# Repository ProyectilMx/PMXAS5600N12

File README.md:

PMXAS5600N12
Encoder Absoluto basado en el integrado AS5600 con 12 neopixels, configurable a través 
de COM Serial 9600 baudios

PMXAS5600N12 version 1.0 - 25/11/2019
PROYECTIL MX - HAZLO REAL

Modulo de Medicion Angular Absoluta Magnetica, programable mediante comandos UART

Esta provisto de un sensor de la marca AMS, el AS5600, que es un sensor
magnetico rotatorio de posicion con una resolucion de 12 bits, para un
rango por hardware de 4095°, el programa provee de otros 4095° para un
rango maximo total de -4095 a 4095°. Por defecto, el sitema viene en un
rango de 0 a 360°.

La placa contiene un microcontrolador maestro, basado en un ATSAMD21E18
de 32 bits, para realizar todas las mediciones y calculos a una velocidad 
de 96MHz, con este rapido sistema se logran obtener mediciones de hasta
6000RPM con 100% de presicion, tanto en revoluciones como en angulo.
La placa tambien consta de varios pines de salida para obtener funcionalidades
diversas:

PA27 - PA18:
Salidas programables en rangos angulares, programables en nivel alto o
bajo dentro de los mismos. Por defecto vienen con los siguientes limites:
PA27 -> de 0° a 90°
PA22 -> de 90° a 180°
PA19 -> de 180° a 270°
PA18 -> de 270° a 360°.
Con estas salidas se puede emular un registro de corrimiento de 4 bits o
activar subsistemas dentro de cierto angulo.

PA14, PA09:
Salidas que generan un pulso de 10us con cada revolucion. 
PA14 -> genera un pulso en el sentido de las manecillas del reloj. 
PA09 -> genera un pulso en el sentido contrario a las manecillas del reloj.

PA05:
Genera una señal PWM con una frecuencia variable entre 1 KHz y 4MHz, con un
ciclo de trabajo configurable entre 0 - 100%, dependiendo de la posicion angular.

PA02:
Genera una señal analogica de 10 bits, de entre 0 y 3.3v aproximadamente, 
dependiendo de la posicion angular.

PA07:
Se puede configurar para activarse dentro de un rango determinado de vueltas. 
Por ejemplo, si se configura que PA07 este en HIGH cuando se este entre 
0 y 500 vueltas, el pulso cambiara a LOW si el numero de vueltas esta fuera 
de ese intervalo.

PA06:
Se puede configurar para que al llegar a un multiplo de vueltas, por ejemplo, 15,  se de 
un pulso de un tiempo configurable en HIGH, por lo tanto este pulso sucederia en 0, 15,
30, 45, 60, 75.... vueltas.

PA04, PA03, PA01, PA00.
Salidas/Entradas: 
Estos pines solamente pueden ser entradas o salidas digitales.

Las funciones de la placa que se encuentran disponibles para el usuraio son:

void pmxas5600n12_configure(void);    - Configura todos los perifericos de la placa
void pmxas5600n12_exe(void);          - Ejecuta todas las acciones de control pertinentes a la placa

Se pueden utilizar las siguiente variables en el programa principal para interactuar con la placa:
 
user_turn       -  Reporta el numero de vueltas actual
user_angle      -  Reporta el angulo actual en 12 bits (0 - 4095)

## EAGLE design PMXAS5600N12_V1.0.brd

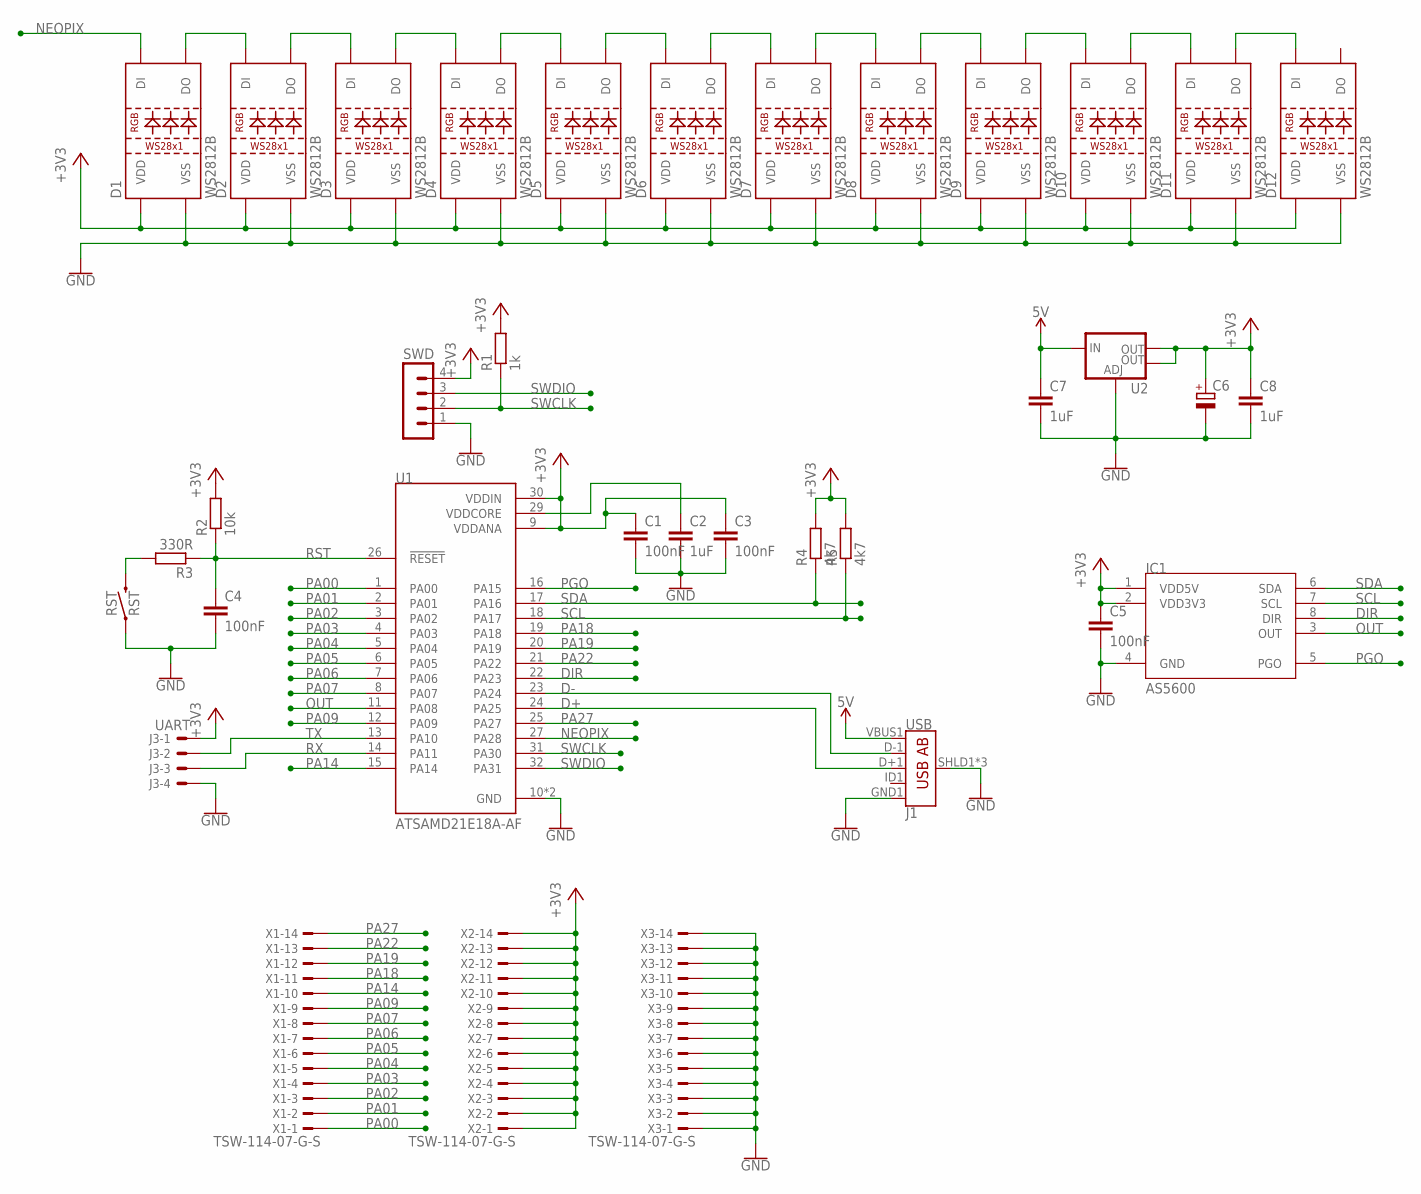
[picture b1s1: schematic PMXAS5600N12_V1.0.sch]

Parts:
C1, C3, C4, C5: 100nF; C0603
C2, C7, C8: 1uF; C0603
C6: CPOL-EU153CLV-0605; 153CLV-0605
D1, D2, D3, D4, D5, D6, D7, D8, D9, D10, D11, D12: WS2812B
IC1: AS5600; SOIC8
J1: USB; USB-AB-MICRO-SMD
J3: UART; 7395-04
R1: 1k; R0603
R2: 10k; R0603
R3: 330R; R0603
R4, R5: 4k7; R0603
RST: RST; TACTILE_SWITCH_SMD_5.2MM
SWD: MA04-1
U1: ATSAMD21E18A-AF; QFP80P900X900X120-32N
U2: V_REG_LM1117SOT223; SOT223
X1, X2, X3: TSW-114-07-G-S; TSW-114-XX-G-S

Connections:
5V: C7.1, J1.VBUS1 (VBUS), U2.3 (IN)
+3V3: C1.1, C3.1, C5.1, C6.+, C8.1, D1.1 (VDD), D2.1 (VDD), D3.1 (VDD), D4.1 (VDD), D5.1 (VDD), D6.1 (VDD), D7.1 (VDD), D8.1 (VDD), D9.1 (VDD), D10.1 (VDD), D11.1 (VDD), D12.1 (VDD), IC1.1 (VDD5V), IC1.2 (VDD3V3), J3.1, R1.2, R2.2, R4.2, R5.2, SWD.4, U1.9 (VDDANA), U1.30 (VDDIN), U2.2 (OUT), U2.4 (OUT), X2.1, X2.2, X2.3, X2.4, X2.5, X2.6, X2.7, X2.8, X2.9, X2.10, X2.11, X2.12, X2.13, X2.14
D+: J1.D+1 (D+), U1.24 (PA25)
D-: J1.D-1 (D-), U1.23 (PA24)
DIR: IC1.8 (DIR), U1.22 (PA23)
GND: C1.2, C2.2, C3.2, C4.2, C5.2, C6.-, C7.2, C8.2, D1.3 (VSS), D2.3 (VSS), D3.3 (VSS), D4.3 (VSS), D5.3 (VSS), D6.3 (VSS), D7.3 (VSS), D8.3 (VSS), D9.3 (VSS), D10.3 (VSS), D11.3 (VSS), D12.3 (VSS), IC1.4 (GND), J1.GND1 (GND), J1.SHLD1 (SHIELD), J1.SHLD2 (SHIELD), J1.SHLD3 (SHIELD), J3.4, RST.1, SWD.1, U1.10 (GND), U1.28 (GND), U2.1 (ADJ), X3.1, X3.2, X3.3, X3.4, X3.5, X3.6, X3.7, X3.8, X3.9, X3.10, X3.11, X3.12, X3.13, X3.14
unnamed: D1.2 (DO), D2.4 (DI)
unnamed: D2.2 (DO), D3.4 (DI)
unnamed: D3.2 (DO), D4.4 (DI)
unnamed: D4.2 (DO), D5.4 (DI)
unnamed: D5.2 (DO), D6.4 (DI)
unnamed: D6.2 (DO), D7.4 (DI)
unnamed: D7.2 (DO), D8.4 (DI)
unnamed: D8.2 (DO), D9.4 (DI)
unnamed: D9.2 (DO), D10.4 (DI)
unnamed: D10.2 (DO), D11.4 (DI)
unnamed: D11.2 (DO), D12.4 (DI)
unnamed: R3.2, RST.3 (2)
NEOPIX: D1.4 (DI), U1.27 (PA28)
OUT: IC1.3 (OUT), U1.11 (PA08)
PA00: U1.1 (PA00), X1.1
PA01: U1.2 (PA01), X1.2
PA02: U1.3 (PA02), X1.3
PA03: U1.4 (PA03), X1.4
PA04: U1.5 (PA04), X1.5
PA05: U1.6 (PA05), X1.6
PA06: U1.7 (PA06), X1.7
PA07: U1.8 (PA07), X1.8
PA09: U1.12 (PA09), X1.9
PA14: U1.15 (PA14), X1.10
PA18: U1.19 (PA18), X1.11
PA19: U1.20 (PA19), X1.12
PA22: U1.21 (PA22), X1.13
PA27: U1.25 (PA27), X1.14
PGO: IC1.5 (PGO), U1.16 (PA15)
RST: C4.1, R2.1, R3.1, U1.26 (!RESET)
RX: J3.3, U1.14 (PA11)
SCL: IC1.7 (SCL), R5.1, U1.18 (PA17)
SDA: IC1.6 (SDA), R4.1, U1.17 (PA16)
SWCLK: R1.1, SWD.2, U1.31 (PA30)
SWDIO: SWD.3, U1.32 (PA31)
TX: J3.2, U1.13 (PA10)
VDDCORE: C2.1, U1.29 (VDDCORE)

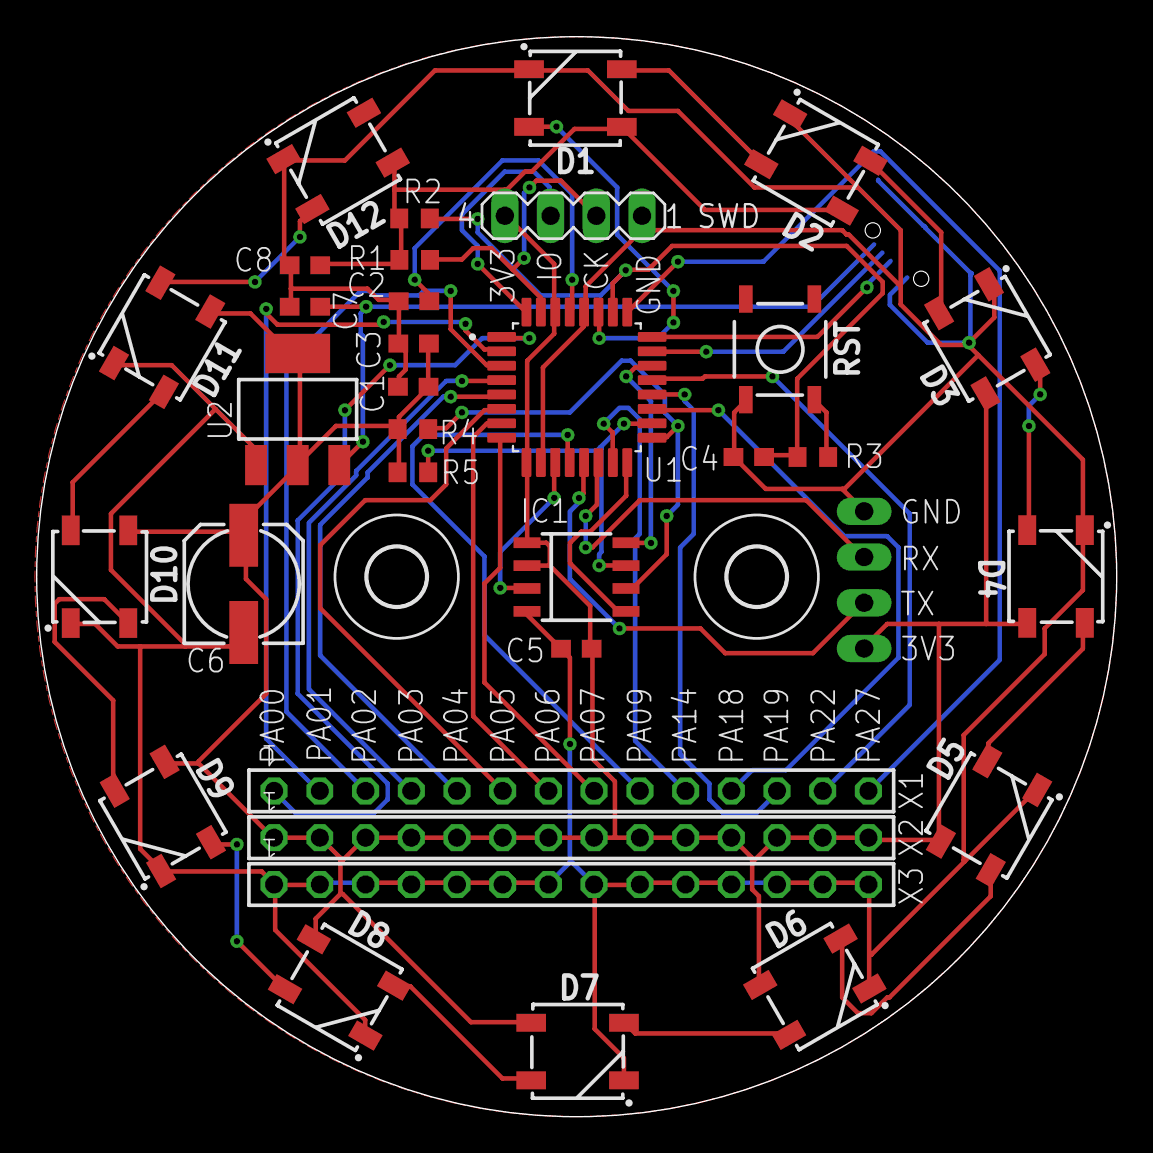
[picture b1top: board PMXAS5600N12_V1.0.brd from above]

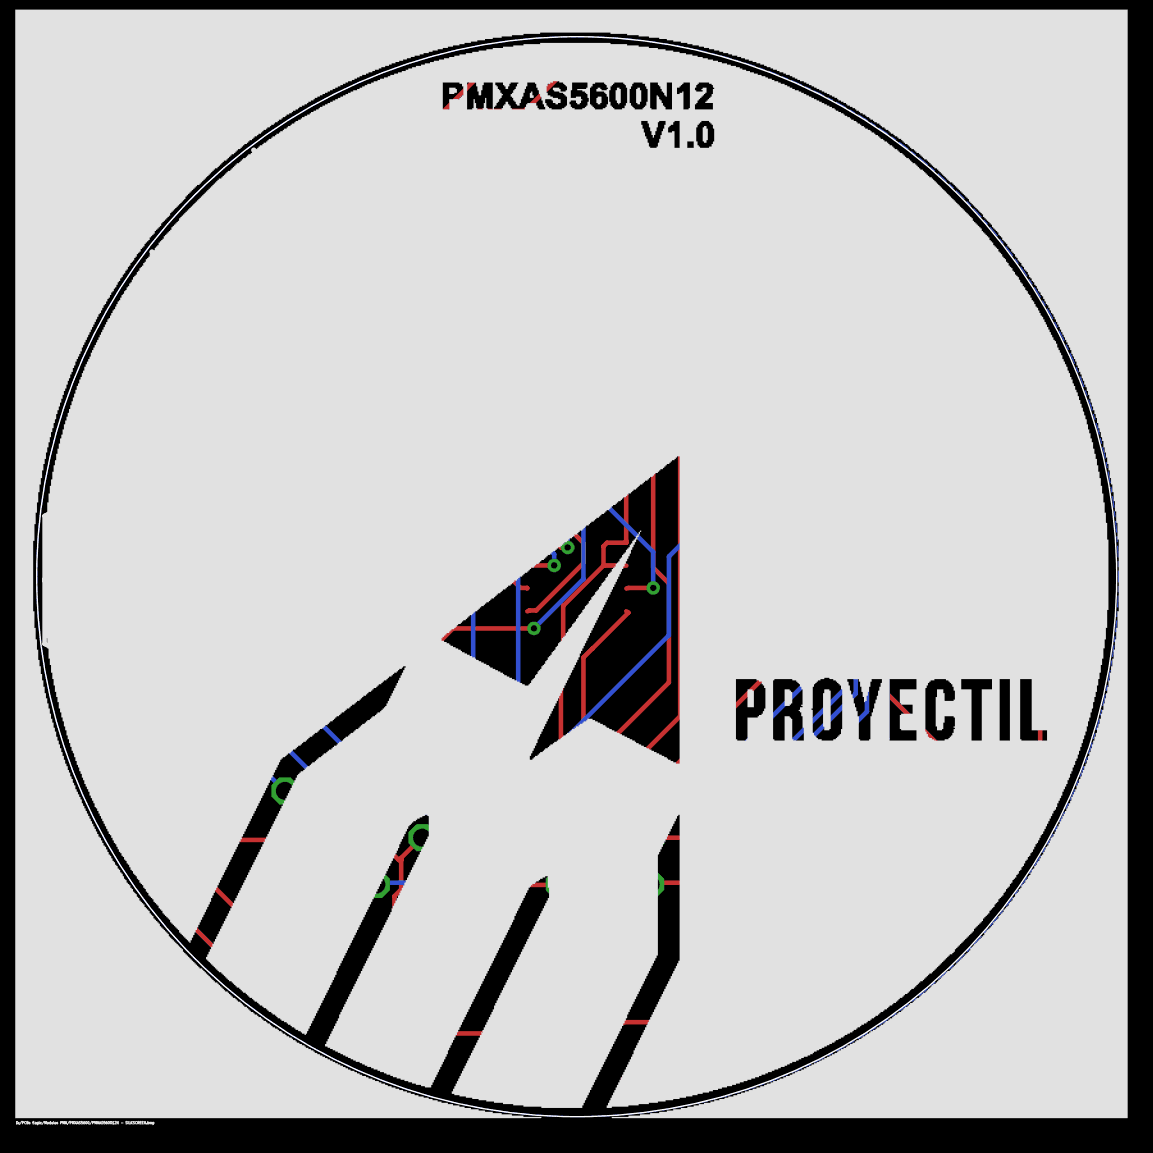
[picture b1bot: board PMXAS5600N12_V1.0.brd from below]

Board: 2 copper layers, 60.0 x 60.0 mm, 37 parts (2 on the bottom side), 43 nets.

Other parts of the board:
U$1, U$2: 3,2

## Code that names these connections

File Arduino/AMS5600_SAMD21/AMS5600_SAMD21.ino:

/*
 * PMXAS5600N12 - Version 1.1 - 28/02/2019
 * Modulo de Medicion Angular Absoluta Magnetica, programable mediante comandos UART
 * La velocidad por defecto es de 9600 baudios
 * 
 * Esta provisto de un sensor de la marca AMS, el AS5600, que es un sensor
 * magnetico rotatorio de posicion con una resolucion de 12 bits, para un
 * rango por hardware de 4095°, el programa provee de otros 4095° para un
 * rango maximo total de -4095 a 4095°. Por defecto, el sitema viene en un
 * rango de 0 a 360°.
 * 
 * La placa contiene un microcontrolador maestro, basado en un ATSAMD21E18
 * de 32 bits, para realizar todas las mediciones y calculos a una velocidad 
 * de 96MHz, con este rapido sistema se logran obtener mediciones de hasta
 * 6000RPM con 100% de presicion, tanto en revoluciones como en angulo.
 * La placa tambien consta de varios pines de salida para obtener funcionalidades
 * diversas:
 * 
 * PA27 - PA18:
 * Salidas programables en rangos angulares, programables en nivel alto o
 * bajo dentro de los mismos. Por defecto vienen con los siguientes limites:
 * PA27 -> de 0° a 90°
 * PA22 -> de 90° a 180°
 * PA19 -> de 180° a 270°
 * PA18 -> de 270° a 360°.
 * Con estas salidas se pueden activar subsistemas dentro de cierto angulo.
 * 
 * PA14, PA09:
 * Salidas que generan un pulso de 10us con cada revolucion. 
 * PA14 -> genera un pulso en el sentido de las manecillas del reloj. 
 * PA09 -> genera un pulso en el sentido contrario a las manecillas del reloj.
 * 
 * PA07:
 * Se puede configurar para activarse dentro de un rango determinado de vueltas. 
 * Por ejemplo, si se configura que PA07 este en HIGH cuando se este entre 
 * 0 y 500 vueltas, el pulso cambiara a LOW si el numero de vueltas esta fuera 
 * de ese intervalo.
 * 
 * PA06:
 * Se puede configurar para que al llegar a un multiplo de vueltas, por ejemplo, 15,
 * cambie a un estado bajo o alto, por lo tanto este pulso sucederia durante la vuelta 
 * 0, 15, 30, 45, 60, 75, etc.
 * 
 * PA05:
 * Genera una señal PWM con una frecuencia de 2.5KHz, con un ciclo de trabajo 
 * configurable entre 0 - 100%, que dependera de la posicion angular.
 * 
 * PA02:
 * Genera una señal analogica de 10 bits, de entre 0 y 3.3v, cuyo valor dependera 
 * de la posicion angular.
 * 
 * PA04, PA03, PA01, PA00.
 * Salidas/Entradas: 
 * Estos pines solamente pueden ser entradas o salidas digitales.
 * 
 * Las funciones de la placa que se encuentran disponibles para el programa principal son:
 * 
 * void pmxas5600n12_configure(void);    - Configura todos los perifericos de la placa
 * void pmxas5600n12_exe(void);          - Ejecuta todas las acciones de control pertinentes a la placa
 * 
 * Se pueden utilizar las siguiente variables en el programa principal para interactuar con la placa:
 * 
 * user_turn       -  Reporta el numero de vueltas actual 
 * user_angle      -  Reporta el angulo actual en 12 bits (0 - 4095)
 */

#include "PMXAS5600N12.h"

void setup() {
  pmxas5600n12_configure();   // Configura todos los perifericos de la placa
  
  /* Si deseas utilizar los pines PA04, PA03, PA01, PA00, deberas descomentarlos y
   * declararlos como entradas o salidas a continuacion
  
  pinMode(PA00, OUTPUT);
  pinMode(PA01, INPUT);
  pinMode(PA03, INPUT);
  pinMode(PA04, INPUT);*/
}

void loop() {
  pmxas5600n12_exe();   // Ejecuta todas las acciones de control pertinentes a la placa

  /* esta linea imprime angulo y vueltas, asegurate que la placa no este reportando nada por 
   * serial antes de descomentarla. Puedes desactivar el envio constante con set,update,call;
   */
  //Serial.println("Vueltas: " + String(user_turn) + ", Angulo: " + String(user_angle));
  
  /*
   * Tu codigo aqui
   */
}

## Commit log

2019-11-01 Add files via upload
    En esta carpeta se encuentran los archivos Variant para una configuración de Arduino más avanzada
2019-11-25 Se lanza la versión publica de PMXAS5600N12
    - Se corrigieron algunos bugs
    - Se implementó nueva funcionalidad en los pines PA06 y PA07
    - Se bajó la velocidad por defecto a 9600 bauds.
    - Se habilitó el Serial1 para poder comunicarse con otra placa.
2019-11-25 Actializacion de Readme con nuevas funciones
2019-11-25 Corrección de errores Ortográficos
2019-11-25 Cambios en la descripción de la placa PMXAS5600N12
2019-11-25 Corrección ortográfica
2019-11-25 Cambio de caracteres de separación y termino
    Otros Cambios menores

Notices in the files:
parts and their libraries:
SparkFun-LED: Licensing: Creative Commons ShareAlike 4.0 International - https://creativecommons.org/licenses/by-sa/4.0
